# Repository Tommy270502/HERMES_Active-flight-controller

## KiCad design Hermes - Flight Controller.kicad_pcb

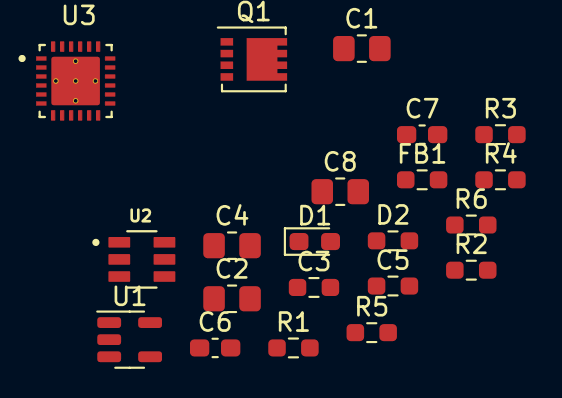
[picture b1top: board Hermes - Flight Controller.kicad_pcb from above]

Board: 2 copper layers, 21 parts (0 on the bottom side), 16 nets, no tracks yet.

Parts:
C1, C2, C4, C8: 100u; R_0805_2012Metric_Pad1.20x1.40mm_HandSolder
C3, C5: 100n; R_0603_1608Metric_Pad0.98x0.95mm_HandSolder
C6, C7: 10u; C_0603_1608Metric_Pad1.08x0.95mm_HandSolder
D1: CHRG; LED_0603_1608Metric_Pad1.05x0.95mm_HandSolder
D2: LED; R_0603_1608Metric_Pad0.98x0.95mm_HandSolder
FB1: 100R@100MHz; R_0603_1608Metric_Pad0.98x0.95mm_HandSolder
Q1: DMP3013SFV; Diodes_PowerDI3333-8
R1, R2, R3, R5, R6: 5.1k; R_0603_1608Metric_Pad0.98x0.95mm_HandSolder
R4: 300R; R_0603_1608Metric_Pad0.98x0.95mm_HandSolder
U1: AP2127K-3.3; SOT-23-5
U2: USBLC6-2SC6; SOT95P280X145-6N
U3: BQ25887RGER; IC_BQ25887RGER

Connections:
+3V3: C4.1, C5.1, R4.2, U1.5 (VOUT)
+5V: C7.1, FB1.2, R3.1
+BATT: Q1.1 (S), Q1.2 (S), Q1.3 (S)
/VSYS: C1.1, C2.1, C3.1, Q1.5 (D), R2.1, U1.1 (VIN)
GND: C1.2, C2.2, C3.2, C4.2, C5.2, C6.2, C7.2, C8.2, D1.1 (K), D2.1 (K), R5.2, R6.2, U1.2 (GND), U2.2
unnamed: C8.1, R2.2, U1.3 (EN)
unnamed: D1.2 (A), R3.2
unnamed: D2.2 (A), R4.1
unnamed: Q1.4 (G), R1.2
unnamed: U3.13 (BAT), U3.14 (BAT)
unnamed: U3.15 (SNS), U3.16 (SNS)
unnamed: U3.17 (SW), U3.18 (SW)
unnamed: U3.19 (GND), U3.20 (GND)
unnamed: U3.21 (PMID), U3.22 (PMID)
unnamed: U3.25 (EXP), U3.26 (EXP), U3.27 (EXP), U3.28 (EXP), U3.29 (EXP), U3.30 (EXP)
VBUS: C6.1, FB1.1, U2.5

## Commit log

2023-01-28 testing repo
2023-01-28 connector
2023-01-28 usbc implementation
2023-01-28 added battery charge circuit
2023-01-29 opting for 2S battery config
2023-01-29 added pmic
2023-01-30 battery mngmt
2023-01-30 2s2p config -> more powa
2023-01-30 rp2040
